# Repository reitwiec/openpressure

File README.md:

# Open Pressure Sensing Device

Reitwiec Shandilya, Michelle Hui, Sebastian Bidegain, Joey Castillo (Cornell Tech). Carson Gundlach and Dr. David Otterburn (Weill Cornell Medicine)

A handheld, open-source instrument designed to measure tactile pressure thresholds digitally. Adapted from clinical tools like the AcroVal™ system, it applies calibrated pressure to the skin and records sensory responses for studies of nerve regeneration following reconstructive surgery.

This project supports the ongoing research of Dr. David Otterburn and Carson Gundlach at Weill Cornell Medicine, whose work in neurotization seeks to restore sensory nerve connections following breast reconstruction surgery. After mastectomy, patients often experience a loss of sensation that affects comfort, safety, and quality of life. Through surgical co-aptation of donor and recipient nerves, Dr. Otterburn’s team aims to re-establish sensory pathways; however, evaluating the success of that process has long relied on subjective or coarse analog tools.
Developed by Cornell Tech Master’s students Michelle Hui and Reitwiec Shandilya in the Cornell Tech MakerLab, this open-source device captures quantitative measurements of tactile pressure (in g/mm²). By precisely logging patient response data, it allows clinicians to objectively track sensory recovery over time, providing richer, reproducible data than traditional Semmes-Weinstein monofilaments, which only measure at discrete force intervals. Beyond reconstructive surgery, the same sensing tool could inform other clinical neurological testing and research functions, expanding open-source tools for quantifying sensation and nerve function.

The project is supported by the Cornell Tech MakerLab and is undertaken in partnership with the Open Source Hardware Association’s Open Healthware Initiative, with the support of the National Science Foundation. The goal is to create a validated, open-source alternative to proprietary devices such as the AcroVal™ Neurosensory & Motor Testing System, enabling wider adoption of transparent, reproducible clinical instrumentation across research and education.

## Features

- **Real-time pressure readings** via USB serial connection
- **Session management** - Create, view, and export patient sessions
- **5 readings per session** with ability to re-record any reading
- **Historical trend visualization** - Track pressure changes across sessions
- **Device calibration** - Built-in calibration workflow
- **CSV export** - Export sessions for external analysis
- **Offline operation** - All data stored locally

## Prerequisites

### Hardware
- KB2040 microcontroller (or compatible CircuitPython board)
- HX711 load cell amplifier
- Load cell sensor
- USB cable

### Software
- Node.js 18+ and npm
- macOS (for building the Mac app)

## Installation

### For Development

```bash
# Clone or copy the project
cd pressure-monitor

# Install dependencies
npm install

# Run in development mode
npm run dev
```

### Building for Distribution

```bash
# Build the Mac application
npm run build:mac

# The installer will be in the `release` folder
```

The build creates:
- `Pressure Monitor-1.0.0.dmg` - Drag-and-drop installer
- `Pressure Monitor-1.0.0-mac.zip` - Portable version

## Firmware Setup

Copy both files from the `firmware/` folder to your KB2040:

```
firmware/
├── code.py      # Main firmware (runs automatically)
└── hx711.py     # HX711 driver library
```

### Installation
1. Connect your KB2040 via USB
2. It should appear as a drive called `CIRCUITPY`
3. Copy `code.py` and `hx711.py` to the root of that drive
4. The device will automatically restart and begin running

### Pin Configuration (in code.py)
- `DT_PIN = board.GP5` - HX711 Data
- `SCK_PIN = board.GP6` - HX711 Clock  
- `BTN_PIN = board.GP16` - Button (uses internal pull-up)

## Usage

### 1. Connect the Device
1. Plug in the KB2040 via USB
2. Open Pressure Monitor
3. Select the serial port from the right panel
4. Click to connect

### 2. Calibration (First Time Setup)
1. Click "Calibrate" in the top bar
2. Long-press the device button (≥0.7 seconds) to start
3. Follow the on-screen steps:
   - Remove all load and press button
   - Place calibration mass and press button
4. Calibration is saved until device restart

### 3. Taking Readings
1. Create a new session (add optional notes)
2. Press the device button to take a reading
3. Click on an empty slot to save the reading
4. Repeat until all 5 slots are filled

### 4. Viewing History
1. Click "History" in the sidebar
2. View trend graph of average readings across sessions
3. Toggle between stress (g/mm²) and weight (g) views

### 5. Exporting Data
1. Select a session
2. Click "Export CSV" in the top bar
3. Choose save location

## Data Storage

All data is stored in `~/PressureReadings/`:
- `session_[timestamp].csv` - Reading data
- `session_[timestamp]_meta.json` - Session metadata

CSV format:
```csv
slot,timestamp,grams,stress_g_mm2
1,2025-01-15T14:30:05,45.2,117.5
2,2025-01-15T14:30:45,44.8,116.4
...
```

## Configuration

Settings are available in the connection panel:
- **Wire Diameter (mm)** - Used for stress calculation
- **Calibration Mass (g)** - Reference mass for calibration

## Troubleshooting

### Device not showing up
- Ensure the KB2040 is properly connected
- Try a different USB cable
- Check if CircuitPython is running (should show as a serial device)

### Readings not appearing
- Verify the serial connection is established (green indicator)
- Check the Device Log for error messages
- Ensure the firmware is running correctly

### Calibration issues
- Make sure to remove ALL load during tare
- Use a precise calibration mass
- Keep the sensor stable during calibration

## License

MIT License - See LICENSE file for details.

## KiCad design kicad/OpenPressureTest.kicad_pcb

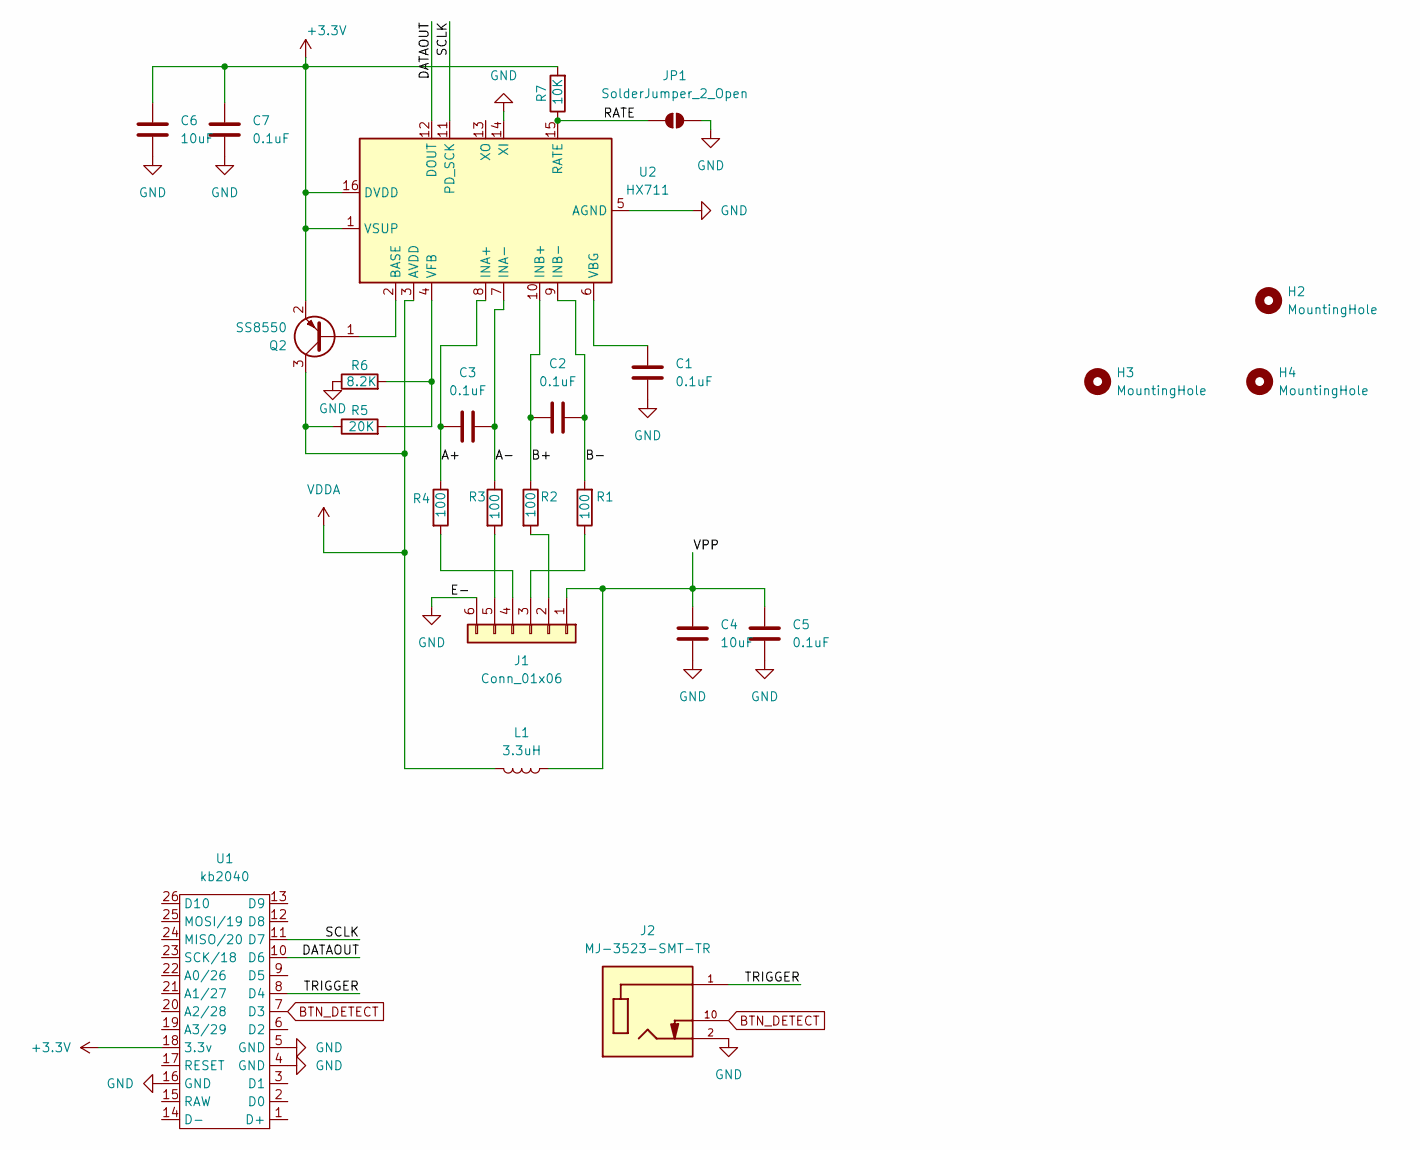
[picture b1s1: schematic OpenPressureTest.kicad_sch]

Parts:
C1, C2, C3, C5, C7: 0.1uF; C_0805_2012Metric; LCSC Part C49678
C4, C6: 10uF; C_0805_2012Metric; LCSC Part C15850
H2, H3, H4: MountingHole; MountingHole_2.2mm_M2
J1: Conn_01x06; PinHeader_1x06_P2.54mm_Vertical
J2: MJ-3523-SMT-TR; CUI_MJ-3523-SMT-TR; PARTREV 1.04; LCSC Part C4992553
JP1: SolderJumper_2_Open; SolderJumper-2_P1.3mm_Open_TrianglePad1.0x1.5mm
L1: 3.3uH; L_0603_1608Metric; LCSC Part C275346
Q2: SS8550; SOT-23; LCSC Part C8542
R1, R2, R3, R4: 100; R_0805_2012Metric; LCSC Part C17408
R5: 20K; R_0805_2012Metric; LCSC Part C4328
R6: 8.2K; R_0805_2012Metric; LCSC Part C17828
R7: 10K; R_0805_2012Metric; LCSC Part C17414
U1: kb2040; kb2040_SMT
U2: HX711; SOIC-16_3.9x9.9mm_P1.27mm; LCSC Part C6705483

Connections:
+3.3V: C6.1, C7.1, Q2.2 (E), R7.2, U1.18 (3.3v), U2.1 (VSUP), U2.16 (DVDD)
/A+: C3.1, R4.1, U2.8 (INA+)
/A-: C3.2, R3.1, U2.7 (INA-)
/B+: C2.1, R2.1, U2.10 (INB+)
/B-: C2.2, R1.2, U2.9 (INB-)
/DATAOUT: U1.10 (D6), U2.12 (DOUT)
/RATE: JP1.1 (A), R7.1, U2.15 (RATE)
/SCLK: U1.11 (D7), U2.11 (PD_SCK)
/TRIGGER: J2.1, U1.8 (D4)
/VPP: C4.1, C5.1, J1.1, L1.1
BTN_DETECT: J2.10, U1.7 (D3)
GND: C1.2, C4.2, C5.2, C6.2, C7.2, J1.6, J2.2, JP1.2 (B), R6.1, U1.4 (GND), U1.5 (GND), U1.16 (GND), U2.5 (AGND), U2.14 (XI)
unnamed: J1.2, R2.2
unnamed: J1.3, R1.1
unnamed: J1.4, R4.2
unnamed: J1.5, R3.2
unnamed: Q2.1 (B), U2.2 (BASE)
unnamed: C1.1, U2.6 (VBG)
unnamed: R5.2, R6.2, U2.4 (VFB)
VDDA: L1.2, Q2.3 (C), R5.1, U2.3 (AVDD)

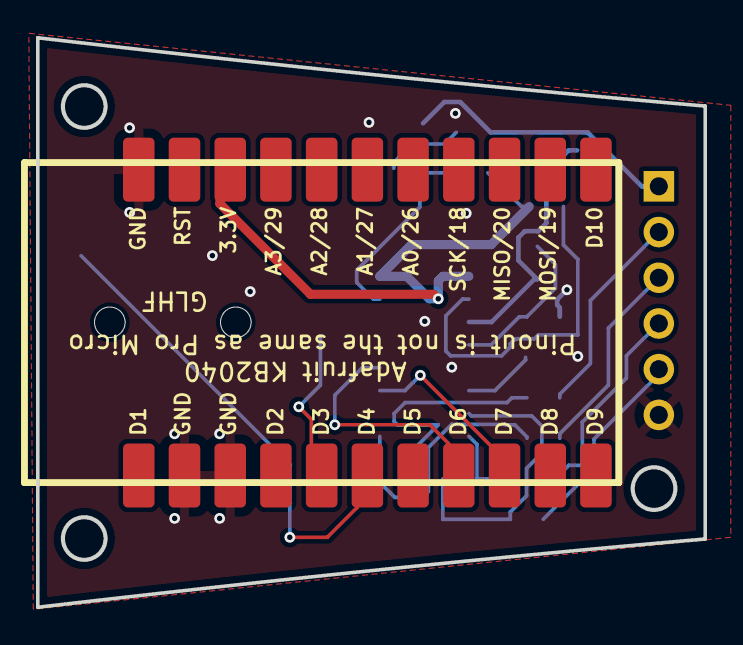
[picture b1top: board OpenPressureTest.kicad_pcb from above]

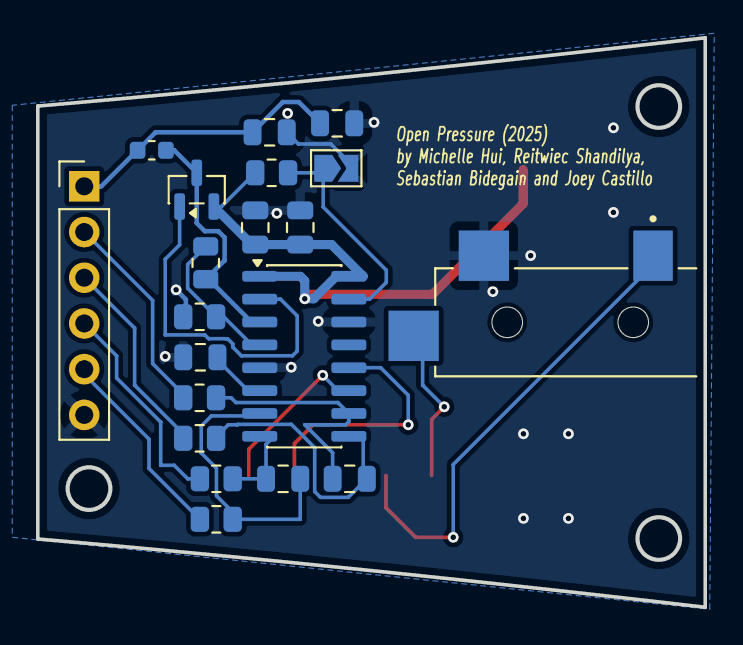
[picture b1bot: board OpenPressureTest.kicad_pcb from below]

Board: 4 copper layers, 37.1 x 31.6 mm, 24 parts (20 on the bottom side), 20 nets.

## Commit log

2025-10-10 Added self callib
2025-11-24 Modified for kb2040
2025-11-30 feat: added code and kicad files
2025-11-30 feat: fixed readme
2025-11-30 fix: improved the readme
